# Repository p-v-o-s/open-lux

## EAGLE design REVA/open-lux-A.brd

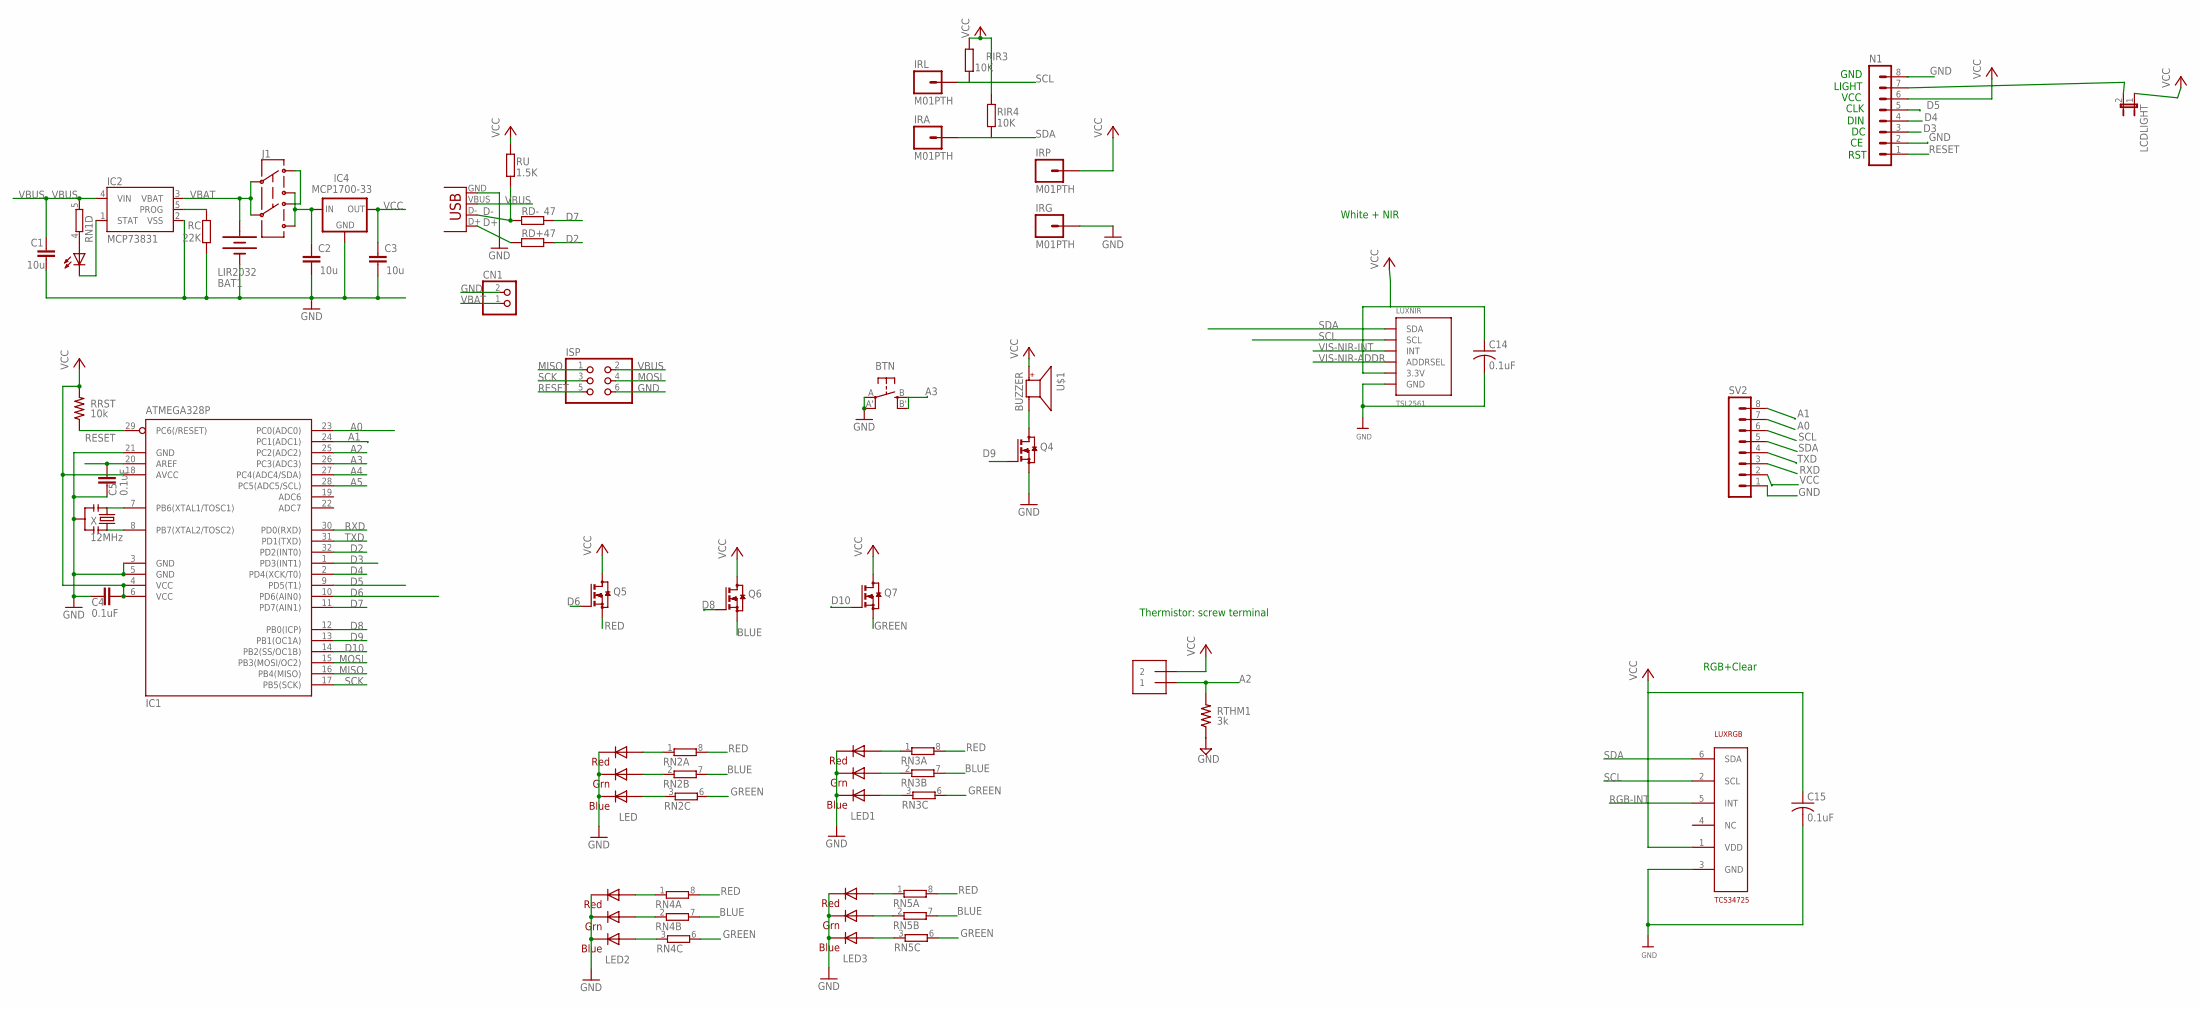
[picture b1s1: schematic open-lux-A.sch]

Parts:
BAT1: LIR2032; BATTCOM_20MM_PTH_SMT
BTN: EVQQ2; EVQ-Q2
C1, C2, C3: 10u; C0805
C4, C5, C14, C15: 0.1uF; C0805
CHG: 0805; CHIPLED_0805
CN1: JST_2PIN-SMT-RA; JST-PH-2-SMT-RA
IC1: ATMEGA328P; TQFP32-08
IC2: MCP73831; SOT23-5
IC4: MCP1700-33; SOT23
IRA: M01PTH; 1X01
IRG: M01PTH; 1X01
IRL: M01PTH; 1X01
IRP: M01PTH; 1X01
ISP: PINHD-2X3; 2X03
J1: AYZ0202
LCDLIGHT: JP1E; JP1
LED, LED1, LED2, LED3: RGBLED5050
LUXNIR: TSL2561; TSL2561_FN@1
LUXRGB: TCS34725; DFN-6
N1: MA08-1
Q4, Q5, Q6, Q7: BSS123; SOT23
RC: 22K; R0805
RD+: 47; R0805
RD-: 47; R0805
RIR3, RIR4: 10K; R0805
RN1, RN2, RN3, RN4, RN5: 4R-NEXB38V; EXB38V
RRST: 10k; R0805@1
RTHM1: 3k; R0805@1
RU: 1.5K; R0805
SV2: MA08-1
THM1: 1X2-3.5MM
U$1: BUZZER; SMT-8585-BUZZER
X: 12MHz; RESONATOR-SMD
X1: USBSMD; USB-MINIB

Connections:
A0: IC1.23 (PC0(ADC0)), SV2.7
A1: IC1.24 (PC1(ADC1)), SV2.8
A2: IC1.25 (PC2(ADC2)), RTHM1.2, THM1.1
A3: BTN.B (S), BTN.B' (S1), IC1.26 (PC3(ADC3))
A4: IC1.27 (PC4(ADC4/SDA))
A5: IC1.28 (PC5(ADC5/SCL))
AREF: C5.2, IC1.20 (AREF)
BLUE: Q6.2 (S), RN2.7 (2), RN3.7 (2), RN4.7 (2), RN5.7 (2)
D2: IC1.32 (PD2(INT0)), RD+.2
D3: IC1.1 (PD3(INT1)), N1.3
D4: IC1.2 (PD4(XCK/T0)), N1.4
D5: IC1.9 (PD5(T1)), N1.5
D6: IC1.10 (PD6(AIN0)), Q5.1 (G)
D7: IC1.11 (PD7(AIN1)), RD-.2
D8: IC1.12 (PB0(ICP)), Q6.1 (G)
D9: IC1.13 (PB1(OC1A)), Q4.1 (G)
D10: IC1.14 (PB2(SS/OC1B)), Q7.1 (G)
D+: RD+.1, X1.D+
D-: RD-.1, RU.1, X1.D-
GND: BAT1.P$1 (-), BTN.A, BTN.A' (P1), C1.2, C2.2, C3.2, C4.1, C5.1, C14.2, C15.2, CN1.2 (1), IC1.3 (GND), IC1.5 (GND), IC1.21 (GND), IC2.2 (VSS), IC4.1 (GND), IRG.1, ISP.6, LED.4 (BLUE_C), LED.5 (RED_C), LED.6 (GREEN_C), LED1.4 (BLUE_C), LED1.5 (RED_C), LED1.6 (GREEN_C), LED2.4 (BLUE_C), LED2.5 (RED_C), LED2.6 (GREEN_C), LED3.4 (BLUE_C), LED3.5 (RED_C), LED3.6 (GREEN_C), LUXNIR.VSS (GND), LUXRGB.3 (GND), N1.2, N1.8, Q4.2 (S), RC.1, RTHM1.1, SV2.1, X.2, X1.GND
GREEN: Q7.2 (S), RN2.6 (2), RN3.6 (2), RN4.6 (2), RN5.6 (2)
MISO: IC1.16 (PB4(MISO)), ISP.1
MOSI: IC1.15 (PB3(MOSI/OC2)), ISP.4
unnamed: J1.3 (1), J1.6 (4)
unnamed: IC1.7 (PB6(XTAL1/TOSC1)), X.1
unnamed: IC1.8 (PB7(XTAL2/TOSC2)), X.3
unnamed: LED.3 (BLUE_A), RN2.3 (1)
unnamed: CHG.C, IC2.1 (STAT)
unnamed: IC2.5 (PROG), RC.2
unnamed: Q4.3 (D), U$1.-
unnamed: LCDLIGHT.2, N1.7
unnamed: LED.1 (GREEN_A), RN2.2 (1)
unnamed: CHG.A, RN1.4 (1)
unnamed: LED.2 (RED_A), RN2.1
unnamed: LED1.3 (BLUE_A), RN3.3 (1)
unnamed: LED1.1 (GREEN_A), RN3.2 (1)
unnamed: LED1.2 (RED_A), RN3.1
unnamed: LED2.3 (BLUE_A), RN4.3 (1)
unnamed: LED2.1 (GREEN_A), RN4.2 (1)
unnamed: LED2.2 (RED_A), RN4.1
unnamed: LED3.3 (BLUE_A), RN5.3 (1)
unnamed: LED3.1 (GREEN_A), RN5.2 (1)
unnamed: LED3.2 (RED_A), RN5.1
RED: Q5.2 (S), RN2.8 (2), RN3.8 (2), RN4.8 (2), RN5.8 (2)
RESET: IC1.29 (PC6(/RESET)), ISP.5, N1.1, RRST.1
RGB-INT: LUXRGB.5 (INT)
RXD: IC1.30 (PD0(RXD)), SV2.3
SCK: IC1.17 (PB5(SCK)), ISP.3
SCL: IRL.1, LUXNIR.CLK (SCL), LUXRGB.2 (SCL), RIR3.1, SV2.6
SDA: IRA.1, LUXNIR.DATA (SDA), LUXRGB.6 (SDA), RIR4.1, SV2.5
TXD: IC1.31 (PD1(TXD)), SV2.4
VBAT: BAT1.P$2 (+), CN1.1 (2), IC2.3 (VBAT), J1.2, J1.5
VBUS: C1.1, IC2.4 (VIN), ISP.2, RN1.5 (2), X1.VBUS
VCC: C3.1, C4.2, C14.1, C15.1, IC1.4 (VCC), IC1.6 (VCC), IC1.18 (AVCC), IC4.2 (OUT), IRP.1, LCDLIGHT.1, LUXNIR.VDD (3.3V), LUXRGB.1 (VDD), N1.6, Q5.3 (D), Q6.3 (D), Q7.3 (D), RIR3.2, RIR4.2, RRST.2, RU.2, SV2.2, THM1.2, U$1.+
VDD: C2.1, IC4.3 (IN), J1.1 (3), J1.4 (6)
VIS-NIR-ADDR: LUXNIR.ADR (ADDRSEL)
VIS-NIR-INT: LUXNIR.INT

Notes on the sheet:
RGB+Clear
White + NIR
RST
DIN
CLK
VCC
LIGHT
GND
Thermistor: screw terminal

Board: 2 copper layers, 50 parts (2 on the bottom side), 52 nets, no tracks yet.

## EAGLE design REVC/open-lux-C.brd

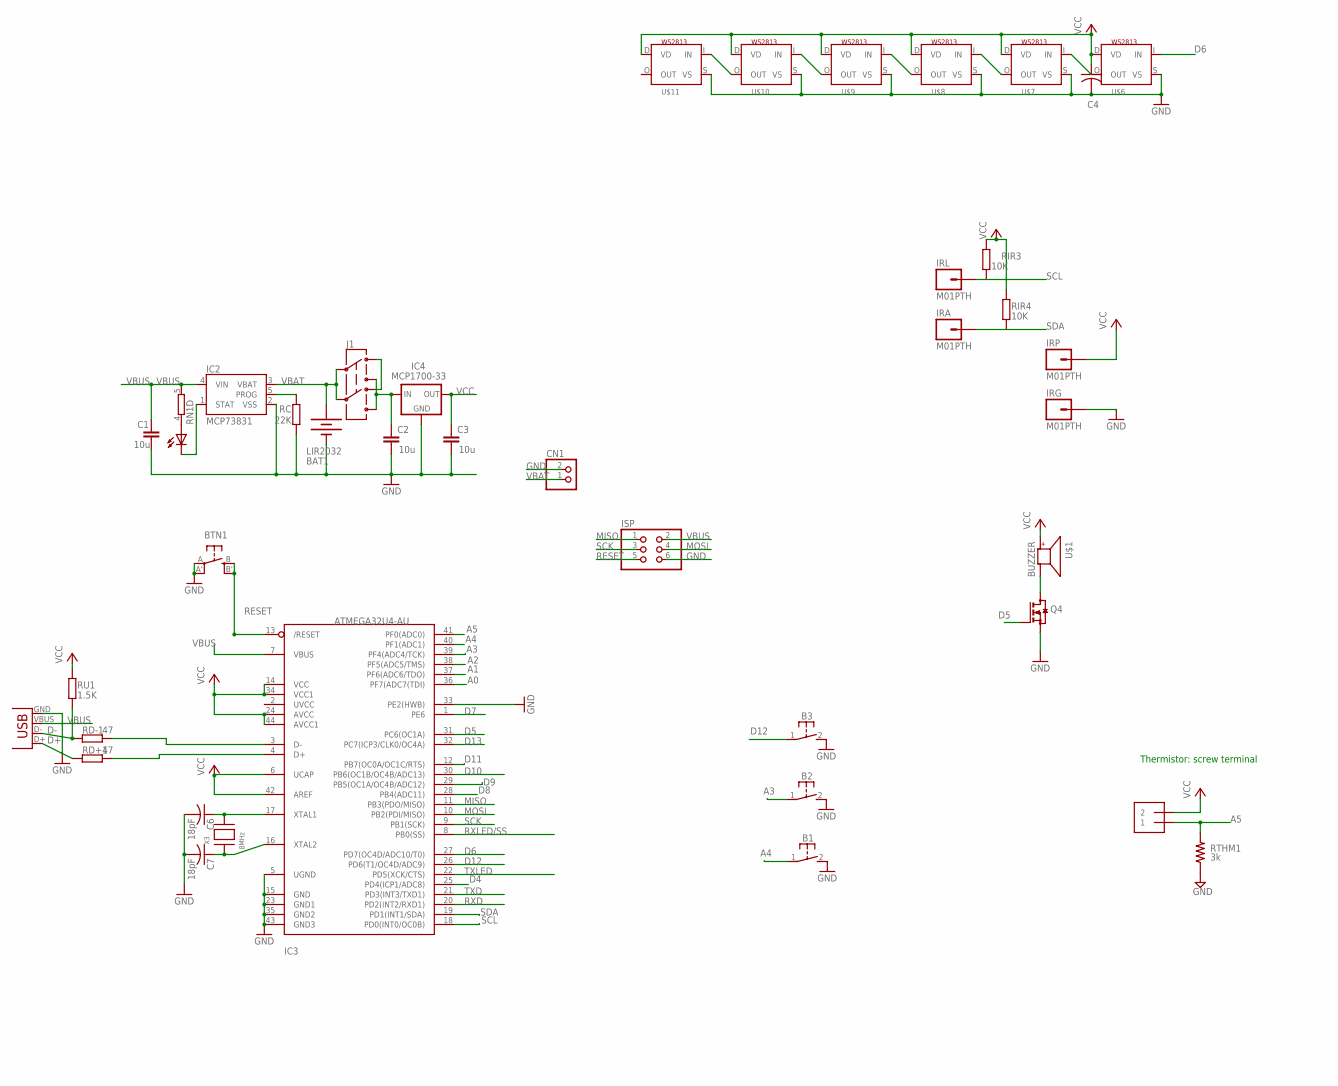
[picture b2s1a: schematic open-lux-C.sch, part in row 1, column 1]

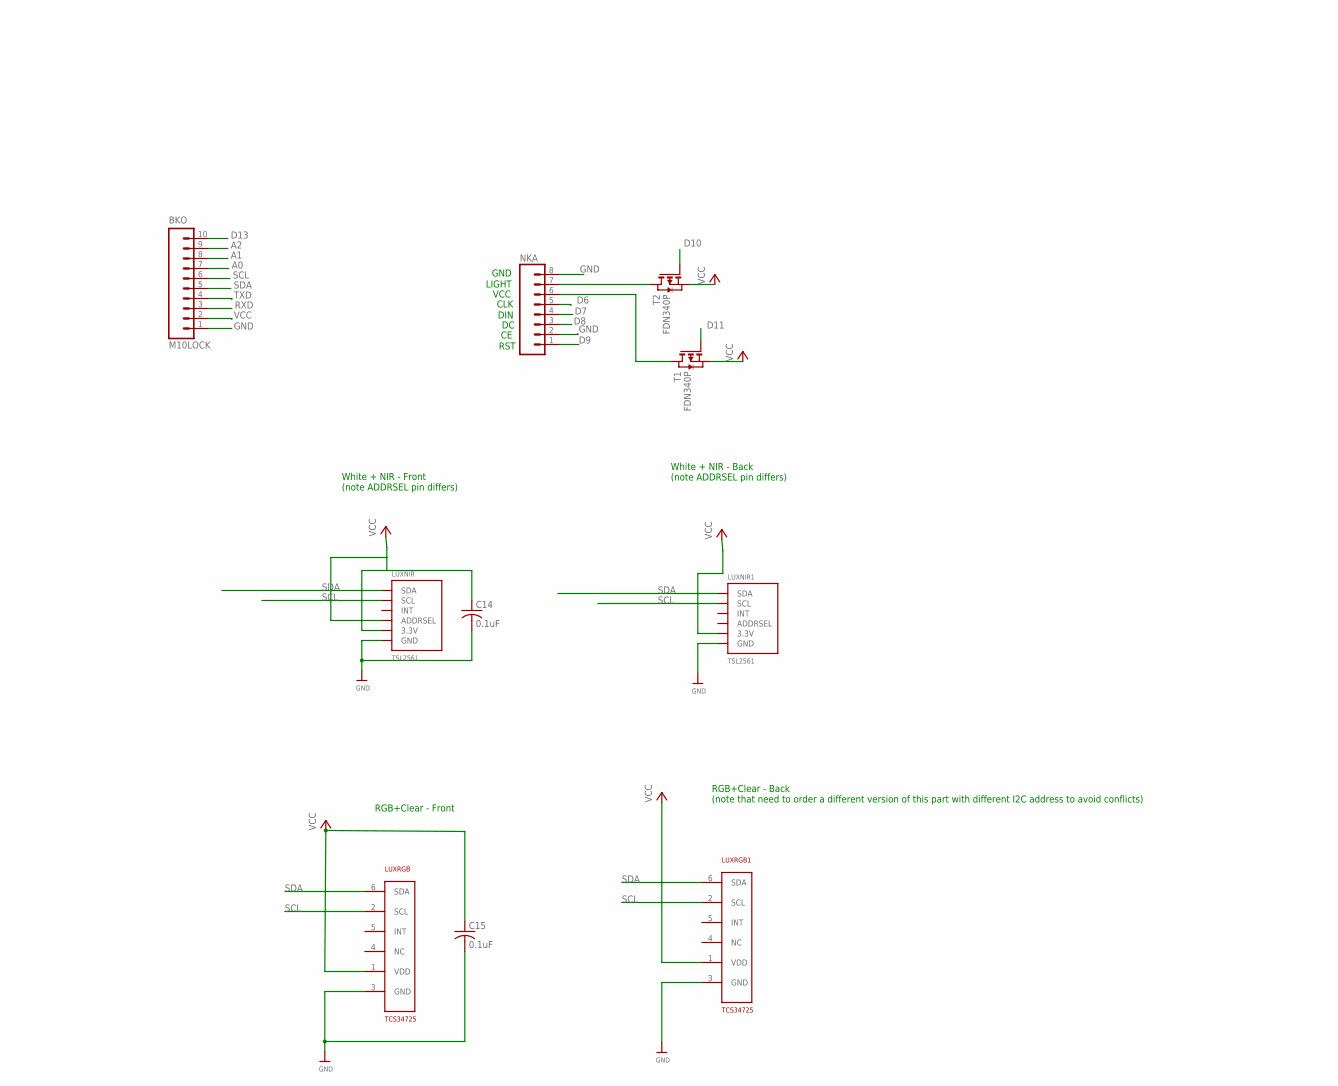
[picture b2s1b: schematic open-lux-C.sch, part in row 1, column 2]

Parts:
B1, B2, B3: 31-XX; B3F-31XX
BAT1: LIR2032; BATTCOM_20MM_PTH_SMT
BKO: M10LOCK; 1X10_LOCK
BTN1: EVQQ2; EVQ-Q2
C1, C2, C3: 10u; C0805
C4: C-USC0805K; C0805K
C6, C7: 18pF; C0805K
C14, C15: 0.1uF; C0805
CHG: 0805; CHIPLED_0805
CN1: JST_2PIN-SMT-RA; JST-PH-2-SMT-RA
IC2: MCP73831; SOT23-5
IC3: ATMEGA32U4-AU; TQFP44
IC4: MCP1700-33; SOT23
IRA: M01PTH; 1X01
IRG: M01PTH; 1X01
IRL: M01PTH; 1X01
IRP: M01PTH; 1X01
ISP: PINHD-2X3; 2X03
J1: AYZ0202
LUXNIR, LUXNIR1: TSL2561; TSL2561_FN@1
LUXRGB, LUXRGB1: TCS34725; DFN-6
NKA: M08LOCK; 1X08_LOCK
Q4: BSS123; SOT23
RC: 22K; R0805
RD+1: 47; R0805
RD-1: 47; R0805
RIR3, RIR4: 10K; R0805
RN1: 4R-NEXB38V; EXB38V
RTHM1: 3k; R0805@1
RU1: 1.5K; R0805
T1, T2: FDN340P; SOT-23
THM1: 1X2-3.5MM
U$1: BUZZER; SMT-8585-BUZZER
U$6, U$7, U$8, U$9, U$10, U$11: WS2813; RGBLED5050_4
X2: USBSMD; USB-MINIB
X3: 8MHz; NX5032

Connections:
A0: BKO.7, IC3.36 (PF7(ADC7(TDI))
A1: BKO.8, IC3.37 (PF6(ADC6/TDO))
A2: BKO.9, IC3.38 (PF5(ADC5/TMS))
A3: B2.1, IC3.39 (PF4(ADC4/TCK))
A4: B1.1, IC3.40 (PF1(ADC1))
A5: IC3.41 (PF0(ADC0)), RTHM1.2, THM1.1
D4: IC3.25 (PD4(ICP1/ADC8))
D5: IC3.31 (PC6(OC1A)), Q4.1 (G)
D6: IC3.27 (PD7(OC4D/ADC10/T0)), NKA.5, U$6.I (IN)
D7: IC3.1 (PE6), NKA.4
D8: IC3.28 (PB4(ADC11)), NKA.3
D9: IC3.29 (PB5(OC1A/OC4B/ADC12)), NKA.1
D10: IC3.30 (PB6(OC1B/OC4B/ADC13)), T2.3 (G)
D11: IC3.12 (PB7(OC0A/OC1C/RTS)), T1.3 (G)
D12: B3.1, IC3.26 (PD6(T1/OC4D/ADC9))
D13: BKO.10, IC3.32 (PC7(ICP3/CLK0/OC4A))
D+: RD+1.1, X2.D+
D-: RD-1.1, RU1.1, X2.D-
GND: B1.2 (S), B2.2 (S), B3.2 (S), BAT1.P$1 (-), BKO.1, BTN1.A, BTN1.A' (P1), C1.2, C2.2, C3.2, C4.2, C6.2, C7.2, C14.2, C15.2, CN1.2 (1), IC2.2 (VSS), IC3.5 (UGND), IC3.15 (GND), IC3.23 (GND1), IC3.33 (PE2(HWB)), IC3.35 (GND2), IC3.43 (GND3), IC4.1 (GND), IRG.1, ISP.6, LUXNIR.VSS (GND), LUXNIR1.VSS (GND), LUXRGB.3 (GND), LUXRGB1.3 (GND), NKA.2, NKA.8, Q4.2 (S), RC.1, RTHM1.1, U$6.S (VS), U$7.S (VS), U$8.S (VS), U$9.S (VS), U$10.S (VS), U$11.S (VS), X2.GND
MISO: IC3.11 (PB3(PDO/MISO)), ISP.1
MOSI: IC3.10 (PB2(PDI/MISO)), ISP.4
unnamed: J1.3 (1), J1.6 (4)
unnamed: C7.1, IC3.16 (XTAL2), X3.P$1
unnamed: C6.1, IC3.17 (XTAL1), X3.P$2
unnamed: NKA.7, T2.1 (D)
unnamed: CHG.C, IC2.1 (STAT)
unnamed: IC2.5 (PROG), RC.2
unnamed: Q4.3 (D), U$1.-
unnamed: NKA.6, T1.1 (D)
unnamed: CHG.A, RN1.4 (1)
unnamed: IC3.4 (D+), RD+1.2
unnamed: IC3.3 (D-), RD-1.2
unnamed: U$6.O (OUT), U$7.I (IN)
unnamed: U$7.O (OUT), U$8.I (IN)
unnamed: U$8.O (OUT), U$9.I (IN)
unnamed: U$9.O (OUT), U$10.I (IN)
unnamed: U$10.O (OUT), U$11.I (IN)
RESET: BTN1.B (S), BTN1.B' (S1), IC3.13 (/RESET), ISP.5
RXD: BKO.3, IC3.20 (PD2(INT2/RXD1))
RXLED/SS: IC3.8 (PB0(SS))
SCK: IC3.9 (PB1(SCK)), ISP.3
SCL: BKO.6, IC3.18 (PD0(INT0/OC0B)), IRL.1, LUXNIR.CLK (SCL), LUXNIR1.CLK (SCL), LUXRGB.2 (SCL), LUXRGB1.2 (SCL), RIR3.1
SDA: BKO.5, IC3.19 (PD1(INT1/SDA)), IRA.1, LUXNIR.DATA (SDA), LUXNIR1.DATA (SDA), LUXRGB.6 (SDA), LUXRGB1.6 (SDA), RIR4.1
TXD: BKO.4, IC3.21 (PD3(INT3/TXD1))
TXLED: IC3.22 (PD5(XCK/CTS))
VBAT: BAT1.P$2 (+), CN1.1 (2), IC2.3 (VBAT), J1.2, J1.5
VBUS: C1.1, IC2.4 (VIN), IC3.7 (VBUS), ISP.2, RN1.5 (2), X2.VBUS
VCC: BKO.2, C3.1, C4.1, C14.1, C15.1, IC3.6 (UCAP), IC3.14 (VCC), IC3.24 (AVCC), IC3.34 (VCC1), IC3.42 (AREF), IC3.44 (AVCC1), IC4.2 (OUT), IRP.1, LUXNIR.ADR (ADDRSEL), LUXNIR.VDD (3.3V), LUXNIR1.VDD (3.3V), LUXRGB.1 (VDD), LUXRGB1.1 (VDD), RIR3.2, RIR4.2, RU1.2, T1.2 (S), T2.2 (S), THM1.2, U$1.+, U$6.D (VD), U$7.D (VD), U$8.D (VD), U$9.D (VD), U$10.D (VD), U$11.D (VD)
VDD: C2.1, IC4.3 (IN), J1.1 (3), J1.4 (6)

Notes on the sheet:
RGB+Clear - Front
White + NIR - Front (note ADDRSEL pin differs)
RST
DIN
CLK
VCC
LIGHT
GND
Thermistor: screw terminal
RGB+Clear - Back (note that need to order a different version of this part with different I2C address to avoid conflicts)
White + NIR - Back (note ADDRSEL pin differs)

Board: 2 copper layers, 51 parts (3 on the bottom side), 46 nets, no tracks yet.

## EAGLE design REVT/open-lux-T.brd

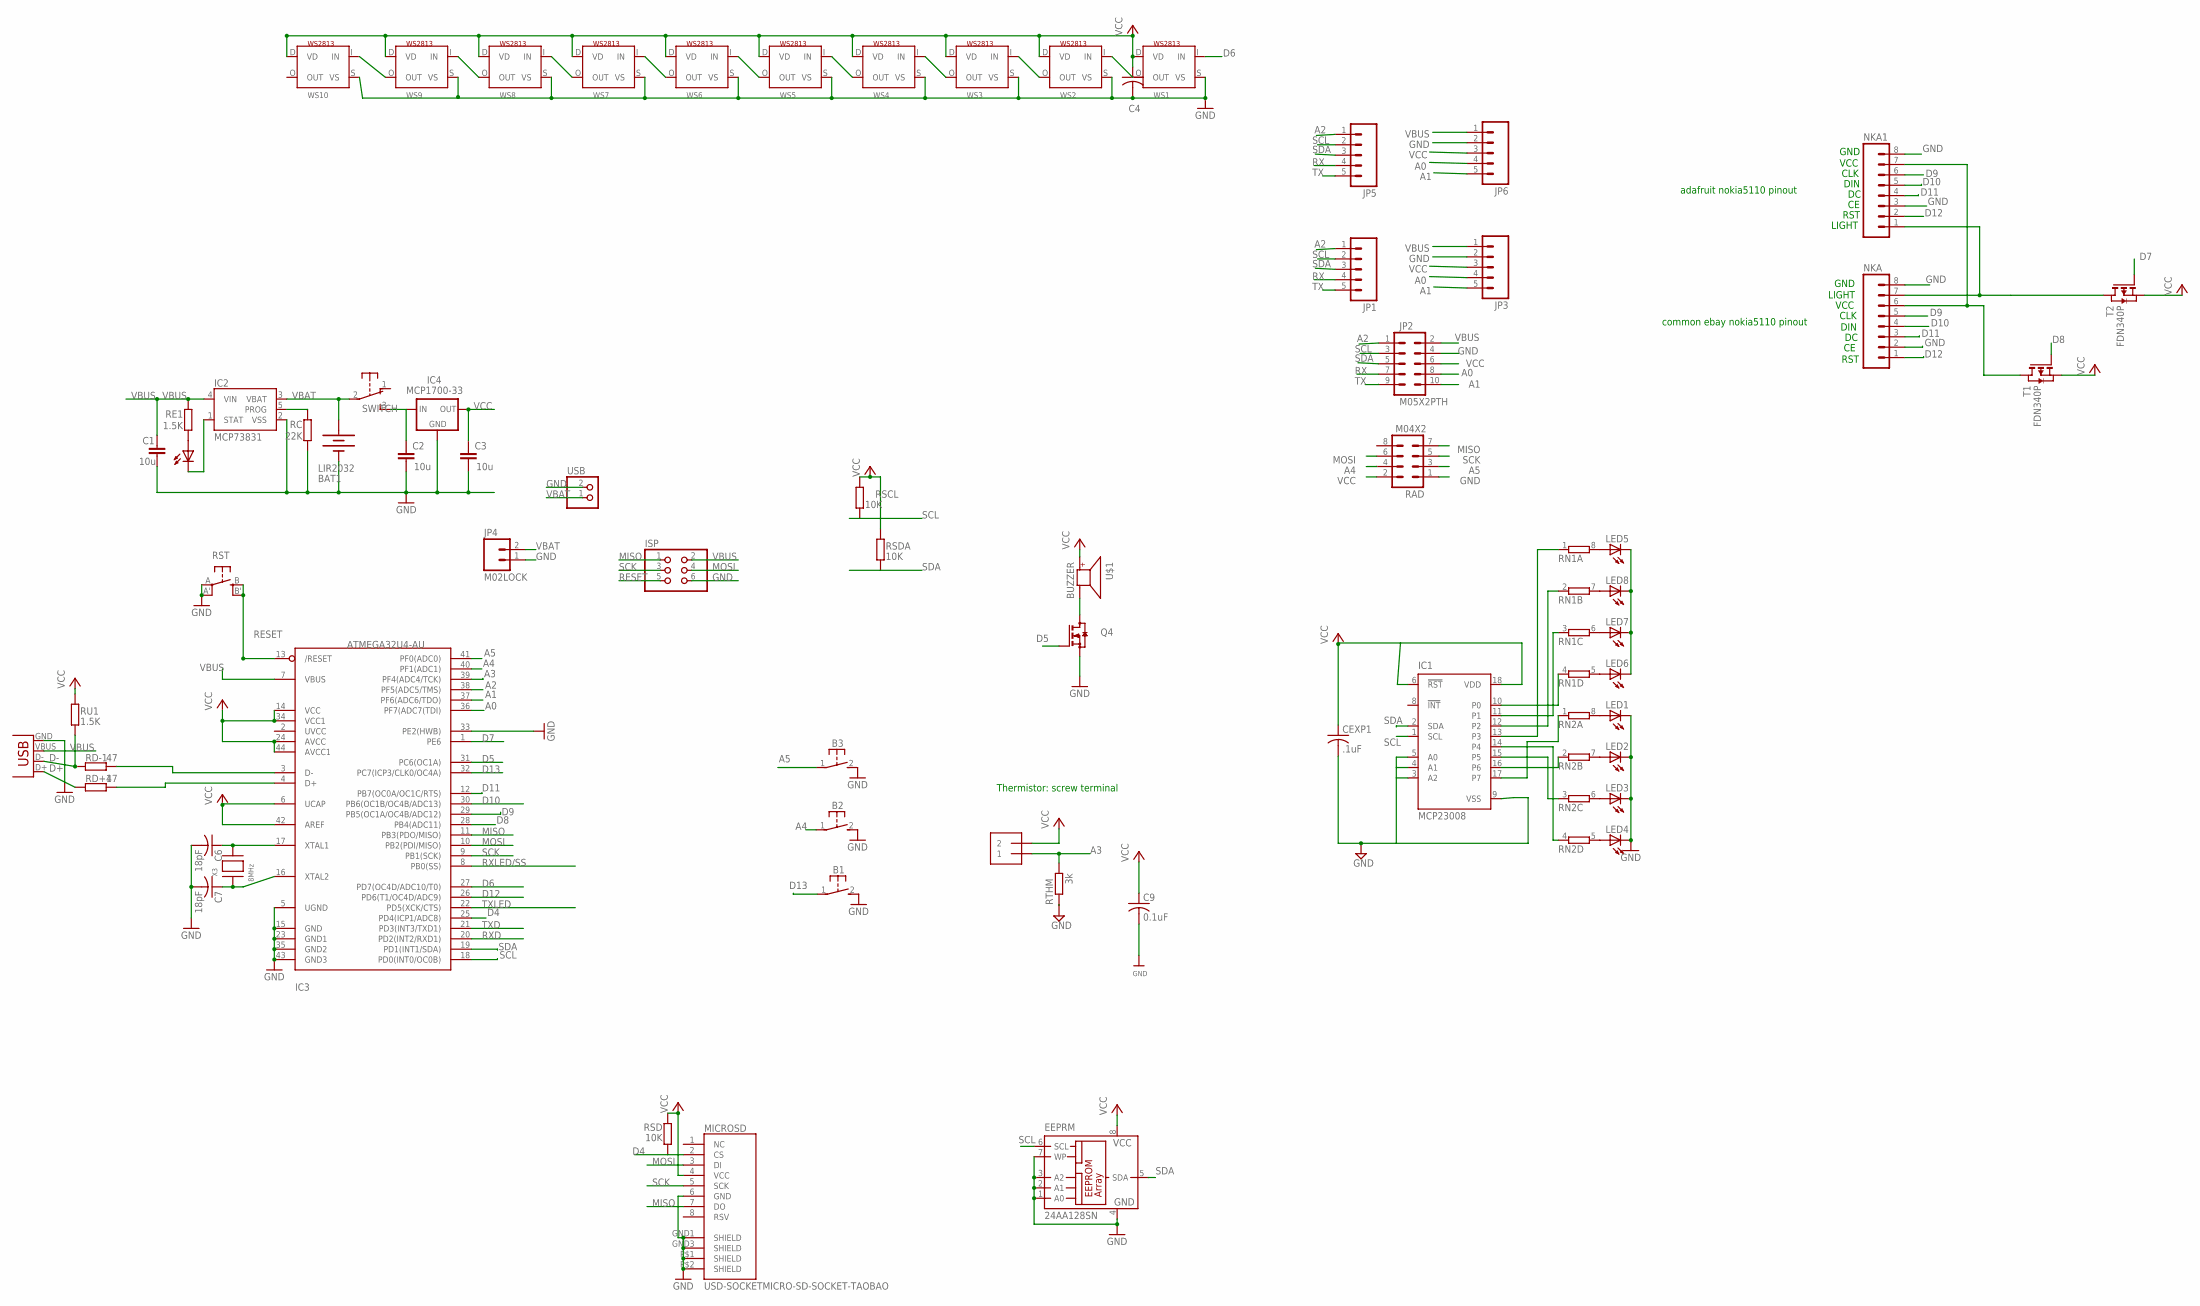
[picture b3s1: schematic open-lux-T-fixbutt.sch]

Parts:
B1, B2, B3: 31-XX; B3F-31XX
BAT1: LIR2032; BATTCOM_20MM_PTH_SMT
C1, C2, C3: 10u; C0805
C4: C-USC0805K; C0805K
C6, C7: 18pF; C0805K
C9: 0.1uF; C0805
CEXP1: .1uF; C0805K
EEPRM: 24AA128SN; SO-08
IC1: MCP23008; SO18W
IC2: MCP73831; SOT23-5
IC3: ATMEGA32U4-AU; TQFP44
IC4: MCP1700-33; SOT23
ISP: PINHD-2X3; 2X03
JP1, JP3, JP5, JP6: M05LOCK; 1X05_LOCK
JP2: M05X2PTH; AVR_ICSP
JP4: M02LOCK; 1X02_LOCK
LED1, LED2, LED3, LED4, LED5, LED6, LED7, LED8: LED3MM
MICROSD: USD-SOCKETMICRO-SD-SOCKET-TAOBAO; MICRO-SD-SOCKET-TAOBAO
NKA, NKA1: M08LOCK; 1X08_LOCK
PWR: 0805; CHIPLED_0805
Q4: BSS123; SOT23
RAD: M04X2; 2X4
RC: 22K; R0805
RD+1: 47; R0805
RD-1: 47; R0805
RE1: 1.5K; R0805
RN1, RN2: 4R-NEXB38V; EXB38V
RSCL: 10K; R0805
RSD: 10K; R0805
RSDA: 10K; R0805
RST: EVQQ2; EVQ-Q2
RTHM: 3k; 0204/7
RU1: 1.5K; R0805
SWITCH: EG1206
T1, T2: FDN340P; SOT-23
THM1: 1X2-3.5MM
U$1: BUZZER; SMT-8585-BUZZER
USB: JST_2PIN-SMT-RA; JST-PH-2-SMT-RA
WS1, WS2, WS3, WS4, WS5, WS6, WS7, WS8, WS9, WS10: WS2813; RGBLED5050_4
X2: USBSMD; USB-MINIB
X3: 8MHz; NX5032

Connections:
A0: IC3.36 (PF7(ADC7(TDI)), JP2.8, JP3.4, JP6.4
A1: IC3.37 (PF6(ADC6/TDO)), JP2.10, JP3.5, JP6.5
A2: IC3.38 (PF5(ADC5/TMS)), JP1.1, JP2.1, JP5.1
A3: IC3.39 (PF4(ADC4/TCK)), RTHM.2, THM1.1
A4: B2.1, IC3.40 (PF1(ADC1)), RAD.4
A5: B3.1, IC3.41 (PF0(ADC0)), RAD.3
D4: IC3.25 (PD4(ICP1/ADC8)), MICROSD.2 (CS), RSD.1
D5: IC3.31 (PC6(OC1A)), Q4.1 (G)
D6: IC3.27 (PD7(OC4D/ADC10/T0)), WS1.I (IN)
D7: IC3.1 (PE6), T2.3 (G)
D8: IC3.28 (PB4(ADC11)), T1.3 (G)
D9: IC3.29 (PB5(OC1A/OC4B/ADC12)), NKA.5, NKA1.6
D10: IC3.30 (PB6(OC1B/OC4B/ADC13)), NKA.4, NKA1.5
D11: IC3.12 (PB7(OC0A/OC1C/RTS)), NKA.3, NKA1.4
D12: IC3.26 (PD6(T1/OC4D/ADC9)), NKA.1, NKA1.2
D13: B1.1, IC3.32 (PC7(ICP3/CLK0/OC4A))
D+: RD+1.1, X2.D+
D-: RD-1.1, RU1.1, X2.D-
GND: B1.2 (S), B2.2 (S), B3.2 (S), BAT1.P$1 (-), C1.2, C2.2, C3.2, C4.2, C6.2, C7.2, C9.2, CEXP1.2, EEPRM.1 (A0), EEPRM.2 (A1), EEPRM.3 (A2), EEPRM.4 (GND), EEPRM.7 (WP), IC1.3 (A2), IC1.4 (A1), IC1.5 (A0), IC1.9 (VSS), IC2.2 (VSS), IC3.5 (UGND), IC3.15 (GND), IC3.23 (GND1), IC3.33 (PE2(HWB)), IC3.35 (GND2), IC3.43 (GND3), IC4.1 (GND), ISP.6, JP2.4, JP3.2, JP4.1, JP6.2, LED1.K (C), LED2.K (C), LED3.K (C), LED4.K (C), MICROSD.6 (GND), MICROSD.GND1 (SHIELD), MICROSD.GND3 (SHIELD), MICROSD.P$1 (SHIELD), MICROSD.P$2 (SHIELD), NKA.2, NKA.8, NKA1.3, NKA1.8, Q4.2 (S), RAD.1, RC.1, RST.A, RST.A' (P1), RTHM.1, USB.2 (1), WS1.S (VS), WS2.S (VS), WS3.S (VS), WS4.S (VS), WS5.S (VS), WS6.S (VS), WS7.S (VS), WS8.S (VS), WS9.S (VS), WS10.S (VS), X2.GND
MISO: IC3.11 (PB3(PDO/MISO)), ISP.1, MICROSD.7 (DO), RAD.7
MOSI: IC3.10 (PB2(PDI/MISO)), ISP.4, MICROSD.3 (DI), RAD.6
unnamed: C2.1, IC4.3 (IN), SWITCH.3 (S)
unnamed: C7.1, IC3.16 (XTAL2), X3.P$1
unnamed: C6.1, IC3.17 (XTAL1), X3.P$2
unnamed: WS9.O (OUT), WS10.I (IN)
unnamed: IC2.1 (STAT), PWR.C
unnamed: IC2.5 (PROG), RC.2
unnamed: Q4.3 (D), U$1.-
unnamed: IC1.14 (P4), RN2.4 (1)
unnamed: PWR.A, RE1.1
unnamed: IC1.15 (P5), RN2.3 (1)
unnamed: NKA.7, NKA1.1
unnamed: IC1.16 (P6), RN2.2 (1)
unnamed: WS6.O (OUT), WS7.I (IN)
unnamed: IC1.17 (P7), RN2.1
unnamed: LED1.A, RN2.8 (2)
unnamed: LED2.A, RN2.7 (2)
unnamed: WS4.O (OUT), WS5.I (IN)
unnamed: WS5.O (OUT), WS6.I (IN)
unnamed: IC3.4 (D+), RD+1.2
unnamed: IC3.3 (D-), RD-1.2
unnamed: WS1.O (OUT), WS2.I (IN)
unnamed: WS2.O (OUT), WS3.I (IN)
unnamed: WS3.O (OUT), WS4.I (IN)
unnamed: LED3.A, RN2.6 (2)
unnamed: WS8.O (OUT), WS9.I (IN)
unnamed: WS7.O (OUT), WS8.I (IN)
unnamed: LED4.A, RN2.5 (2)
unnamed: LED5.K (C), LED6.K (C), LED7.K (C), LED8.K (C)
unnamed: NKA.6, NKA1.7, T1.1 (D)
unnamed: LED5.A, RN1.8 (2)
unnamed: LED6.A, RN1.5 (2)
unnamed: LED7.A, RN1.6 (2)
unnamed: LED8.A, RN1.7 (2)
unnamed: IC1.13 (P3), RN1.1
unnamed: IC1.12 (P2), RN1.2 (1)
unnamed: IC1.11 (P1), RN1.3 (1)
unnamed: IC1.10 (P0), RN1.4 (1)
RESET: IC3.13 (/RESET), ISP.5, RST.B (S), RST.B' (S1)
RX: JP1.4, JP2.7, JP5.4
RXD: IC3.20 (PD2(INT2/RXD1))
RXLED/SS: IC3.8 (PB0(SS))
SCK: IC3.9 (PB1(SCK)), ISP.3, MICROSD.5 (SCK), RAD.5
SCL: EEPRM.6 (SCL), IC1.1 (SCL), IC3.18 (PD0(INT0/OC0B)), JP1.2, JP2.3, JP5.2, RSCL.1
SDA: EEPRM.5 (SDA), IC1.2 (SDA), IC3.19 (PD1(INT1/SDA)), JP1.3, JP2.5, JP5.3, RSDA.1
TX: JP1.5, JP2.9, JP5.5
TXD: IC3.21 (PD3(INT3/TXD1))
TXLED: IC3.22 (PD5(XCK/CTS))
VBAT: BAT1.P$2 (+), IC2.3 (VBAT), JP4.2, SWITCH.2, USB.1 (2)
VBUS: C1.1, IC2.4 (VIN), IC3.7 (VBUS), ISP.2, JP2.2, JP3.1, JP6.1, RE1.2, X2.VBUS
VCC: C3.1, C4.1, C9.1, CEXP1.1, EEPRM.8 (VCC), IC1.6 (!RST), IC1.18 (VDD), IC3.6 (UCAP), IC3.14 (VCC), IC3.24 (AVCC), IC3.34 (VCC1), IC3.42 (AREF), IC3.44 (AVCC1), IC4.2 (OUT), JP2.6, JP3.3, JP6.3, MICROSD.4 (VCC), RAD.2, RSCL.2, RSD.2, RSDA.2, RU1.2, T1.2 (S), T2.2 (S), THM1.2, U$1.+, WS1.D (VD), WS2.D (VD), WS3.D (VD), WS4.D (VD), WS5.D (VD), WS6.D (VD), WS7.D (VD), WS8.D (VD), WS9.D (VD), WS10.D (VD)

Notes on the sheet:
RST
DIN
CLK
VCC
LIGHT
GND
adafruit nokia5110 pinout
common ebay nokia5110 pinout
Thermistor: screw terminal

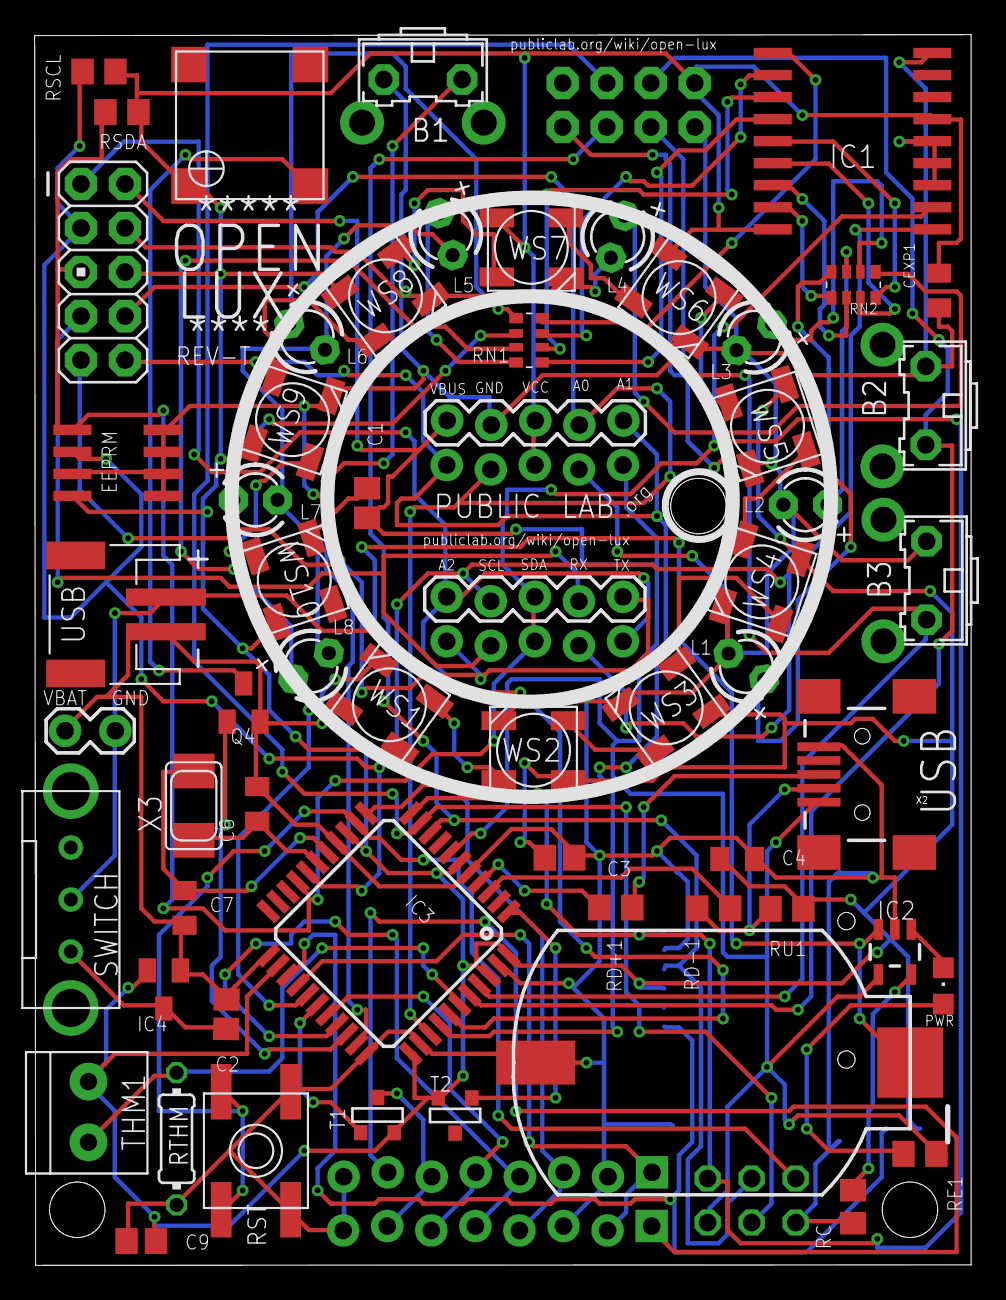
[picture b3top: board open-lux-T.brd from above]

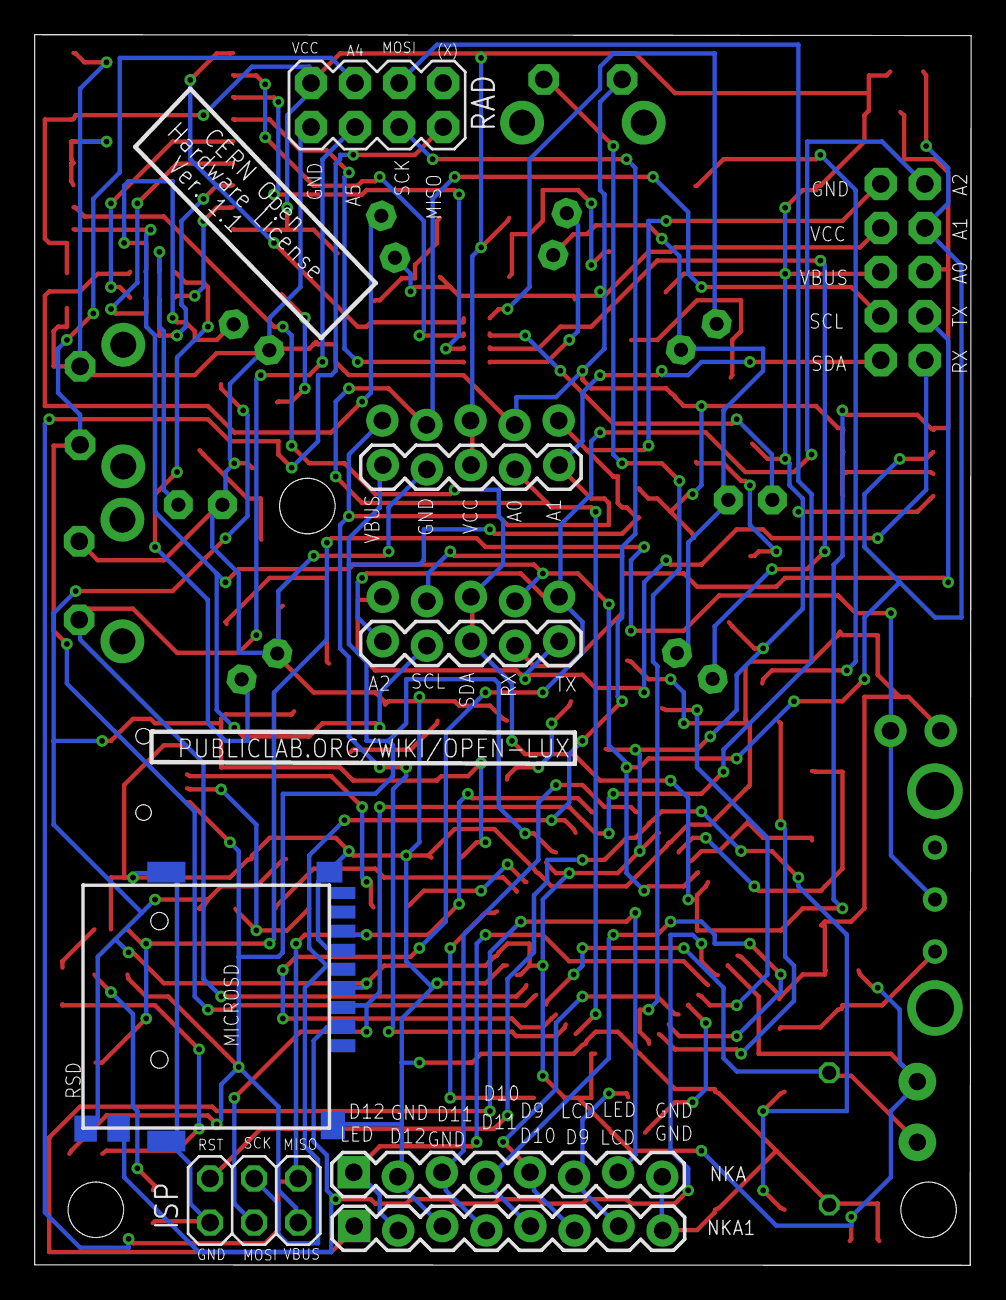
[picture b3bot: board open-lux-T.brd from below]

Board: 2 copper layers, 54.0 x 70.9 mm, 68 parts (8 on the bottom side), 67 nets.

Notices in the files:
REVT/open-lux-T.brd:
Hardware License
parts and their libraries:
microbuilder: This work is placed in the public domain, and may be freely used for commercial and non-commercial work with the following conditions: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
SparkFun-Connectors: Licensing: Creative Commons ShareAlike 4.0 International - https://creativecommons.org/licenses/by-sa/4.0
